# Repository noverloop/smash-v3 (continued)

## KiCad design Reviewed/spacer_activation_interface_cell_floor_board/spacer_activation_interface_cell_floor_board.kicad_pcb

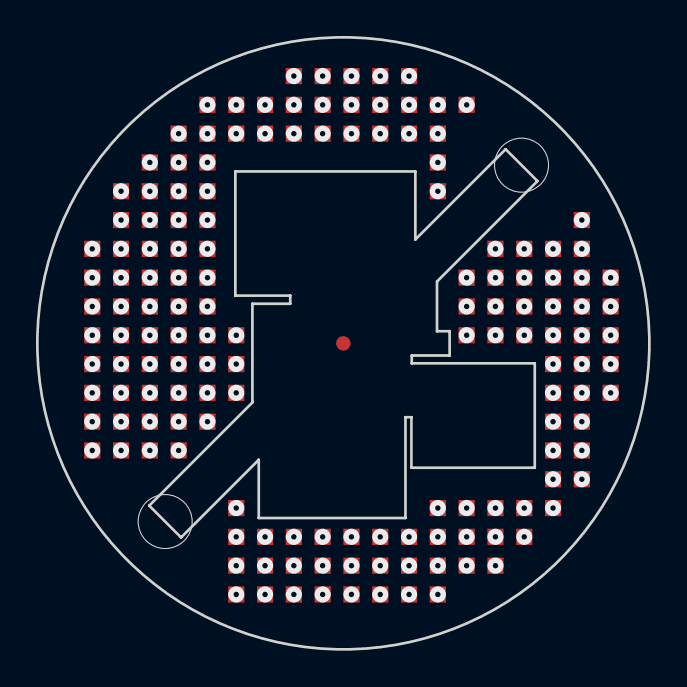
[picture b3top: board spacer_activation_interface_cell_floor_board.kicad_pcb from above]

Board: 2 copper layers, 34.0 x 34.0 mm, 3 parts (1 on the bottom side), 46 nets, no tracks yet.

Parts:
J_spacer_activation_interface_cell_floor_board_top: LGA_lands; J_spacer_activation_interface_cell_floor_board_top
P_spacer_activation_interface_cell_floor_board_bot: LGA_lands; P_spacer_activation_interface_cell_floor_board_bot
SP_activation_interface_cell_floor_board: SP_activation_interface_cell_floor_board; Spacer_Mechanical_34mm

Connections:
3V3: J_spacer_activation_interface_cell_floo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.1, J_spacer_activation_interface_cell_floo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.47, J_spacer_activation_interface_cell_floo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.52, P_spacer_activation_interface_cell_floo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.1, P_spacer_activation_interface_cell_floo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.47, P_spacer_activation_interface_cell_floo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.52
3V3_AON: J_spacer_activation_interface_cell_floo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.2, J_spacer_activation_interface_cell_floo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.48, P_spacer_activation_interface_cell_floo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.2, P_spacer_activation_interface_cell_floo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.48
ACTIVATE_CONFIRM: J_spacer_activation_interface_cell_floo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.3, P_spacer_activation_interface_cell_floo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.3
ACTIVATE_SET: J_spacer_activation_interface_cell_floo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.4, P_spacer_activation_interface_cell_floo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.4
BAT_PROT: J_spacer_activation_interface_cell_floo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.5, J_spacer_activation_interface_cell_floo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.49, P_spacer_activation_interface_cell_floo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.5, P_spacer_activation_interface_cell_floo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.49
BAT_RAW: J_spacer_activation_interface_cell_floo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.6, J_spacer_activation_interface_cell_floo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.50, P_spacer_activation_interface_cell_floo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.6, P_spacer_activation_interface_cell_floo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.50
BOOT0: J_spacer_activation_interface_cell_floo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.7, P_spacer_activation_interface_cell_floo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.7
COMP_5V: J_spacer_activation_interface_cell_floo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.8, J_spacer_activation_interface_cell_floo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.51, P_spacer_activation_interface_cell_floo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.8, P_spacer_activation_interface_cell_floo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.51
COMP_SWDCLK: J_spacer_activation_interface_cell_floo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.9, P_spacer_activation_interface_cell_floo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.9
COMP_SWDIO: J_spacer_activation_interface_cell_floo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.10, P_spacer_activation_interface_cell_floo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.10
EXT_CAN_RX: J_spacer_activation_interface_cell_floo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.11, P_spacer_activation_interface_cell_floo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.11
EXT_CAN_TX: J_spacer_activation_interface_cell_floo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.12, P_spacer_activation_interface_cell_floo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.12
FIN1_AOUT1: J_spacer_activation_interface_cell_floo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.13, P_spacer_activation_interface_cell_floo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.13
FIN1_AOUT2: J_spacer_activation_interface_cell_floo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.14, P_spacer_activation_interface_cell_floo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.14
FIN1_BOUT1: J_spacer_activation_interface_cell_floo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.15, P_spacer_activation_interface_cell_floo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.15
FIN1_BOUT2: J_spacer_activation_interface_cell_floo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.16, P_spacer_activation_interface_cell_floo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.16
FIN2_AOUT1: J_spacer_activation_interface_cell_floo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.17, P_spacer_activation_interface_cell_floo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.17
FIN2_AOUT2: J_spacer_activation_interface_cell_floo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.18, P_spacer_activation_interface_cell_floo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.18
FIN2_BOUT1: J_spacer_activation_interface_cell_floo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.19, P_spacer_activation_interface_cell_floo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.19
FIN2_BOUT2: J_spacer_activation_interface_cell_floo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.20, P_spacer_activation_interface_cell_floo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.20
FIN3_AOUT1: J_spacer_activation_interface_cell_floo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.21, P_spacer_activation_interface_cell_floo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.21
FIN3_AOUT2: J_spacer_activation_interface_cell_floo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.22, P_spacer_activation_interface_cell_floo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.22
FIN3_BOUT1: J_spacer_activation_interface_cell_floo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.23, P_spacer_activation_interface_cell_floo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.23
FIN3_BOUT2: J_spacer_activation_interface_cell_floo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.24, P_spacer_activation_interface_cell_floo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.24
FIN4_AOUT1: J_spacer_activation_interface_cell_floo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.25, P_spacer_activation_interface_cell_floo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.25
FIN4_AOUT2: J_spacer_activation_interface_cell_floo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.26, P_spacer_activation_interface_cell_floo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.26
FIN4_BOUT1: J_spacer_activation_interface_cell_floo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.27, P_spacer_activation_interface_cell_floo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.27
FIN4_BOUT2: J_spacer_activation_interface_cell_floo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.28, P_spacer_activation_interface_cell_floo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.28
FIN_HALL: J_spacer_activation_interface_cell_floo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.29, P_spacer_activation_interface_cell_floo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.29
FLEX_GND: J_spacer_activation_interface_cell_floo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.30, J_spacer_activation_interface_cell_floo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.53, J_spacer_activation_interface_cell_floo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.54, J_spacer_activation_interface_cell_floo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.55, J_spacer_activation_interface_cell_floo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.56, J_spacer_activation_interface_cell_floo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.57, J_spacer_activation_interface_cell_floo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.58, J_spacer_activation_interface_cell_floo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.59, J_spacer_activation_interface_cell_floo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.60, J_spacer_activation_interface_cell_floo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.61, J_spacer_activation_interface_cell_floo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.62, J_spacer_activation_interface_cell_floo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.63, J_spacer_activation_interface_cell_floo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.64, J_spacer_activation_interface_cell_floo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.65, J_spacer_activation_interface_cell_floo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.66, J_spacer_activation_interface_cell_floo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.67, J_spacer_activation_interface_cell_floo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.68, J_spacer_activation_interface_cell_floo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.69, J_spacer_activation_interface_cell_floo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.70, J_spacer_activation_interface_cell_floo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.71, J_spacer_activation_interface_cell_floo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.72, J_spacer_activation_interface_cell_floo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.73, J_spacer_activation_interface_cell_floo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.74, J_spacer_activation_interface_cell_floo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.75, J_spacer_activation_interface_cell_floo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.76, J_spacer_activation_interface_cell_floo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.77, J_spacer_activation_interface_cell_floo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.78, J_spacer_activation_interface_cell_floo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.79, J_spacer_activation_interface_cell_floo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.80, J_spacer_activation_interface_cell_floo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.81, J_spacer_activation_interface_cell_floo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.82, J_spacer_activation_interface_cell_floo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.83, J_spacer_activation_interface_cell_floo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.84, J_spacer_activation_interface_cell_floo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.85, J_spacer_activation_interface_cell_floo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.86, J_spacer_activation_interface_cell_floo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.87, J_spacer_activation_interface_cell_floo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.88, J_spacer_activation_interface_cell_floo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.89, J_spacer_activation_interface_cell_floo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.90, J_spacer_activation_interface_cell_floo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.91, J_spacer_activation_interface_cell_floo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.92, J_spacer_activation_interface_cell_floo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.93, J_spacer_activation_interface_cell_floo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.94, J_spacer_activation_interface_cell_floo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.95, J_spacer_activation_interface_cell_floo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.96, J_spacer_activation_interface_cell_floo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.97, J_spacer_activation_interface_cell_floo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.98, J_spacer_activation_interface_cell_floo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.99, J_spacer_activation_interface_cell_floo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.100, J_spacer_activation_interface_cell_floo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.101, J_spacer_activation_interface_cell_floo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.102, J_spacer_activation_interface_cell_floo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.103, J_spacer_activation_interface_cell_floo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.104, J_spacer_activation_interface_cell_floo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.105, J_spacer_activation_interface_cell_floo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.106, J_spacer_activation_interface_cell_floo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.107, J_spacer_activation_interface_cell_floo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.108, J_spacer_activation_interface_cell_floo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.109, J_spacer_activation_interface_cell_floo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.110, J_spacer_activation_interface_cell_floo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.111, J_spacer_activation_interface_cell_floo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.112, J_spacer_activation_interface_cell_floo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.113, J_spacer_activation_interface_cell_floo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.114, J_spacer_activation_interface_cell_floo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.115, J_spacer_activation_interface_cell_floo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.116, J_spacer_activation_interface_cell_floo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.117, J_spacer_activation_interface_cell_floo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.118, J_spacer_activation_interface_cell_floo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.119, J_spacer_activation_interface_cell_floo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.120, J_spacer_activation_interface_cell_floo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.121, J_spacer_activation_interface_cell_floo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.122, J_spacer_activation_interface_cell_floo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.123, J_spacer_activation_interface_cell_floo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.124, J_spacer_activation_interface_cell_floo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.125, J_spacer_activation_interface_cell_floo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.126, J_spacer_activation_interface_cell_floo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.127, J_spacer_activation_interface_cell_floo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.128, J_spacer_activation_interface_cell_floo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.129, J_spacer_activation_interface_cell_floo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.130, J_spacer_activation_interface_cell_floo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.131, J_spacer_activation_interface_cell_floo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.132, J_spacer_activation_interface_cell_floo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.133, J_spacer_activation_interface_cell_floo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.134, J_spacer_activation_interface_cell_floo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.135, J_spacer_activation_interface_cell_floo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.136, J_spacer_activation_interface_cell_floo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.137, J_spacer_activation_interface_cell_floo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.138, J_spacer_activation_interface_cell_floo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.139, J_spacer_activation_interface_cell_floo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.140, J_spacer_activation_interface_cell_floo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.141, J_spacer_activation_interface_cell_floo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.142, J_spacer_activation_interface_cell_floo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.143, J_spacer_activation_interface_cell_floo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.144, J_spacer_activation_interface_cell_floo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.145, J_spacer_activation_interface_cell_floo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.146, J_spacer_activation_interface_cell_floo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.147, J_spacer_activation_interface_cell_floo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.148, J_spacer_activation_interface_cell_floo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.149, J_spacer_activation_interface_cell_floo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.150, P_spacer_activation_interface_cell_floo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.30, P_spacer_activation_interface_cell_floo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.53, P_spacer_activation_interface_cell_floo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.54, P_spacer_activation_interface_cell_floo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.55, P_spacer_activation_interface_cell_floo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.56, P_spacer_activation_interface_cell_floo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.57, P_spacer_activation_interface_cell_floo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.58, P_spacer_activation_interface_cell_floo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.59, P_spacer_activation_interface_cell_floo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.60, P_spacer_activation_interface_cell_floo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.61, P_spacer_activation_interface_cell_floo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.62, P_spacer_activation_interface_cell_floo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.63, P_spacer_activation_interface_cell_floo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.64, P_spacer_activation_interface_cell_floo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.65, P_spacer_activation_interface_cell_floo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.66, P_spacer_activation_interface_cell_floo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.67, P_spacer_activation_interface_cell_floo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.68, P_spacer_activation_interface_cell_floo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.69, P_spacer_activation_interface_cell_floo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.70, P_spacer_activation_interface_cell_floo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.71, P_spacer_activation_interface_cell_floo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.72, P_spacer_activation_interface_cell_floo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.73, P_spacer_activation_interface_cell_floo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.74, P_spacer_activation_interface_cell_floo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.75, P_spacer_activation_interface_cell_floo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.76, P_spacer_activation_interface_cell_floo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.77, P_spacer_activation_interface_cell_floo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.78, P_spacer_activation_interface_cell_floo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.79, P_spacer_activation_interface_cell_floo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.80, P_spacer_activation_interface_cell_floo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.81, P_spacer_activation_interface_cell_floo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.82, P_spacer_activation_interface_cell_floo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.83, P_spacer_activation_interface_cell_floo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.84, P_spacer_activation_interface_cell_floo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.85, P_spacer_activation_interface_cell_floo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.86, P_spacer_activation_interface_cell_floo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.87, P_spacer_activation_interface_cell_floo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.88, P_spacer_activation_interface_cell_floo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.89, P_spacer_activation_interface_cell_floo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.90, P_spacer_activation_interface_cell_floo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.91, P_spacer_activation_interface_cell_floo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.92, P_spacer_activation_interface_cell_floo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.93, P_spacer_activation_interface_cell_floo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.94, P_spacer_activation_interface_cell_floo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.95, P_spacer_activation_interface_cell_floo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.96, P_spacer_activation_interface_cell_floo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.97, P_spacer_activation_interface_cell_floo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.98, P_spacer_activation_interface_cell_floo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.99, P_spacer_activation_interface_cell_floo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.100, P_spacer_activation_interface_cell_floo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.101, P_spacer_activation_interface_cell_floo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.102, P_spacer_activation_interface_cell_floo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.103, P_spacer_activation_interface_cell_floo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.104, P_spacer_activation_interface_cell_floo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.105, P_spacer_activation_interface_cell_floo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.106, P_spacer_activation_interface_cell_floo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.107, P_spacer_activation_interface_cell_floo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.108, P_spacer_activation_interface_cell_floo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.109, P_spacer_activation_interface_cell_floo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.110, P_spacer_activation_interface_cell_floo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.111, P_spacer_activation_interface_cell_floo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.112, P_spacer_activation_interface_cell_floo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.113, P_spacer_activation_interface_cell_floo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.114, P_spacer_activation_interface_cell_floo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.115, P_spacer_activation_interface_cell_floo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.116, P_spacer_activation_interface_cell_floo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.117, P_spacer_activation_interface_cell_floo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.118, P_spacer_activation_interface_cell_floo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.119, P_spacer_activation_interface_cell_floo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.120, P_spacer_activation_interface_cell_floo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.121, P_spacer_activation_interface_cell_floo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.122, P_spacer_activation_interface_cell_floo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.123, P_spacer_activation_interface_cell_floo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.124, P_spacer_activation_interface_cell_floo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.125, P_spacer_activation_interface_cell_floo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.126, P_spacer_activation_interface_cell_floo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.127, P_spacer_activation_interface_cell_floo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.128, P_spacer_activation_interface_cell_floo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.129, P_spacer_activation_interface_cell_floo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.130, P_spacer_activation_interface_cell_floo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.131, P_spacer_activation_interface_cell_floo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.132, P_spacer_activation_interface_cell_floo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.133, P_spacer_activation_interface_cell_floo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.134, P_spacer_activation_interface_cell_floo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.135, P_spacer_activation_interface_cell_floo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.136, P_spacer_activation_interface_cell_floo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.137, P_spacer_activation_interface_cell_floo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.138, P_spacer_activation_interface_cell_floo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.139, P_spacer_activation_interface_cell_floo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.140, P_spacer_activation_interface_cell_floo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.141, P_spacer_activation_interface_cell_floo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.142, P_spacer_activation_interface_cell_floo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.143, P_spacer_activation_interface_cell_floo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.144, P_spacer_activation_interface_cell_floo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.145, P_spacer_activation_interface_cell_floo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.146, P_spacer_activation_interface_cell_floo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.147, P_spacer_activation_interface_cell_floo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.148, P_spacer_activation_interface_cell_floo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.149, P_spacer_activation_interface_cell_floo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.150, SP_activation_interface_cell_floor_board.1
GPIO_EXT_0: J_spacer_activation_interface_cell_floo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.31, P_spacer_activation_interface_cell_floo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.31
GPIO_EXT_1: J_spacer_activation_interface_cell_floo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.32, P_spacer_activation_interface_cell_floo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.32
GPIO_EXT_2: J_spacer_activation_interface_cell_floo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.33, P_spacer_activation_interface_cell_floo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.33
GPIO_EXT_3: J_spacer_activation_interface_cell_floo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.34, P_spacer_activation_interface_cell_floo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.34
H3LIS_INT1: J_spacer_activation_interface_cell_floo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.35, P_spacer_activation_interface_cell_floo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.35
I2C3_SCL: J_spacer_activation_interface_cell_floo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.36, P_spacer_activation_interface_cell_floo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.36
I2C3_SDA: J_spacer_activation_interface_cell_floo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.37, P_spacer_activation_interface_cell_floo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.37
JUMP_WAKE: J_spacer_activation_interface_cell_floo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.38, P_spacer_activation_interface_cell_floo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.38
NRST: J_spacer_activation_interface_cell_floo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.39, P_spacer_activation_interface_cell_floo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.39
SWO: J_spacer_activation_interface_cell_floo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.40, P_spacer_activation_interface_cell_floo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.40
SYS_I2C_SCL: J_spacer_activation_interface_cell_floo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.41, P_spacer_activation_interface_cell_floo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.41
SYS_I2C_SDA: J_spacer_activation_interface_cell_floo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.42, P_spacer_activation_interface_cell_floo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.42
SYS_SPI_CS_FIN: J_spacer_activation_interface_cell_floo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.43, P_spacer_activation_interface_cell_floo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.43
SYS_SPI_MISO: J_spacer_activation_interface_cell_floo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.44, P_spacer_activation_interface_cell_floo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.44
SYS_SPI_MOSI: J_spacer_activation_interface_cell_floo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.45, P_spacer_activation_interface_cell_floo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.45
SYS_SPI_SCLK: J_spacer_activation_interface_cell_floo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.46, P_spacer_activation_interface_cell_floo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.46

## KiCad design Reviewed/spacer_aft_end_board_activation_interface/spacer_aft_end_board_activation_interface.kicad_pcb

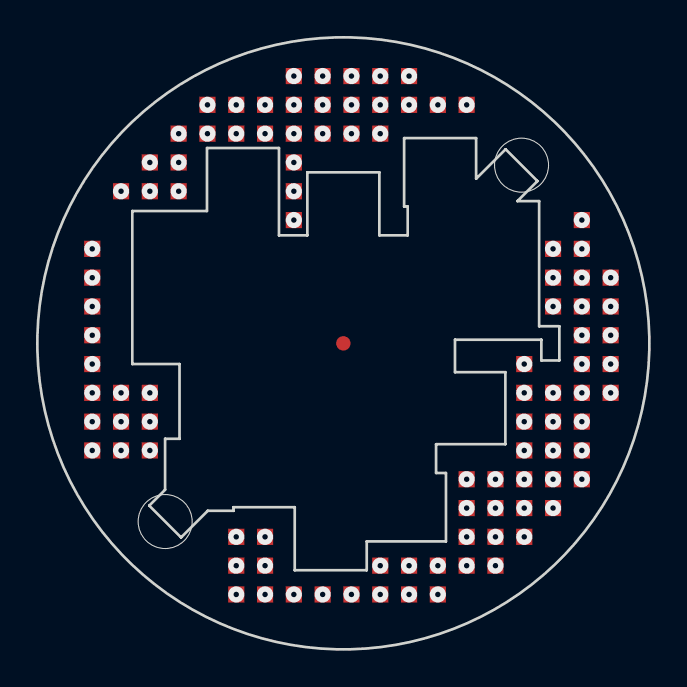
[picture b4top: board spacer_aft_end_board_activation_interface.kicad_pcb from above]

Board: 2 copper layers, 34.0 x 34.0 mm, 3 parts (1 on the bottom side), 44 nets, no tracks yet.

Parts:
J_spacer_aft_end_board_activation_interface_top: LGA_lands; J_spacer_aft_end_board_activation_interface_top
P_spacer_aft_end_board_activation_interface_bot: LGA_lands; P_spacer_aft_end_board_activation_interface_bot
SP_aft_end_board_activation_interface: SP_aft_end_board_activation_interface; Spacer_Mechanical_34mm

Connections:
3V3: J_spacer_aft_end_board_activation_inter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.1, J_spacer_aft_end_board_activation_inter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.45, J_spacer_aft_end_board_activation_inter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.51, P_spacer_aft_end_board_activation_inter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.1, P_spacer_aft_end_board_activation_inter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.45, P_spacer_aft_end_board_activation_inter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.51
3V3_AON: J_spacer_aft_end_board_activation_inter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.2, J_spacer_aft_end_board_activation_inter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.46, P_spacer_aft_end_board_activation_inter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.2, P_spacer_aft_end_board_activation_inter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.46
ACTIVATE_CONFIRM: J_spacer_aft_end_board_activation_inter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.3, P_spacer_aft_end_board_activation_inter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.3
ACTIVATE_HV: J_spacer_aft_end_board_activation_inter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.28, J_spacer_aft_end_board_activation_inter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.50, P_spacer_aft_end_board_activation_inter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.28, P_spacer_aft_end_board_activation_inter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.50
ACTIVATE_SET: J_spacer_aft_end_board_activation_inter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.4, P_spacer_aft_end_board_activation_inter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.4
BAT_PROT: J_spacer_aft_end_board_activation_inter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.5, J_spacer_aft_end_board_activation_inter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.47, P_spacer_aft_end_board_activation_inter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.5, P_spacer_aft_end_board_activation_inter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.47
BAT_RAW: J_spacer_aft_end_board_activation_inter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.6, J_spacer_aft_end_board_activation_inter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.48, P_spacer_aft_end_board_activation_inter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.6, P_spacer_aft_end_board_activation_inter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.48
BOOT0: J_spacer_aft_end_board_activation_inter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.7, P_spacer_aft_end_board_activation_inter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.7
COMP_5V: J_spacer_aft_end_board_activation_inter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.8, J_spacer_aft_end_board_activation_inter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.49, P_spacer_aft_end_board_activation_inter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.8, P_spacer_aft_end_board_activation_inter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.49
COMP_SWDCLK: J_spacer_aft_end_board_activation_inter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.9, P_spacer_aft_end_board_activation_inter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.9
COMP_SWDIO: J_spacer_aft_end_board_activation_inter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.10, P_spacer_aft_end_board_activation_inter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.10
EXT_CAN_RX: J_spacer_aft_end_board_activation_inter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.16, P_spacer_aft_end_board_activation_inter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.16
EXT_CAN_TX: J_spacer_aft_end_board_activation_inter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.12, P_spacer_aft_end_board_activation_inter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.12
FIN1_AOUT1: J_spacer_aft_end_board_activation_inter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.13, P_spacer_aft_end_board_activation_inter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.13
FIN1_AOUT2: J_spacer_aft_end_board_activation_inter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.14, P_spacer_aft_end_board_activation_inter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.14
FIN1_BOUT1: J_spacer_aft_end_board_activation_inter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.15, P_spacer_aft_end_board_activation_inter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.15
FIN1_BOUT2: J_spacer_aft_end_board_activation_inter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.11, P_spacer_aft_end_board_activation_inter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.11
FIN2_AOUT1: J_spacer_aft_end_board_activation_inter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.17, P_spacer_aft_end_board_activation_inter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.17
FIN2_AOUT2: J_spacer_aft_end_board_activation_inter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.18, P_spacer_aft_end_board_activation_inter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.18
FIN2_BOUT1: J_spacer_aft_end_board_activation_inter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.19, P_spacer_aft_end_board_activation_inter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.19
FIN2_BOUT2: J_spacer_aft_end_board_activation_inter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.20, P_spacer_aft_end_board_activation_inter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.20
FIN3_AOUT1: J_spacer_aft_end_board_activation_inter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.21, P_spacer_aft_end_board_activation_inter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.21
FIN3_AOUT2: J_spacer_aft_end_board_activation_inter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.22, P_spacer_aft_end_board_activation_inter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.22
FIN3_BOUT1: J_spacer_aft_end_board_activation_inter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.23, P_spacer_aft_end_board_activation_inter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.23
FIN3_BOUT2: J_spacer_aft_end_board_activation_inter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.24, P_spacer_aft_end_board_activation_inter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.24
FIN4_AOUT1: J_spacer_aft_end_board_activation_inter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.25, P_spacer_aft_end_board_activation_inter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.25
FIN4_AOUT2: J_spacer_aft_end_board_activation_inter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.30, P_spacer_aft_end_board_activation_inter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.30
FIN4_BOUT1: J_spacer_aft_end_board_activation_inter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.27, P_spacer_aft_end_board_activation_inter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.27
FIN4_BOUT2: J_spacer_aft_end_board_activation_inter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.26, P_spacer_aft_end_board_activation_inter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.26
FIN_HALL: J_spacer_aft_end_board_activation_inter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.29, P_spacer_aft_end_board_activation_inter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.29
FLEX_GND: J_spacer_aft_end_board_activation_inter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.31, J_spacer_aft_end_board_activation_inter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.52, J_spacer_aft_end_board_activation_inter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.53, J_spacer_aft_end_board_activation_inter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.54, J_spacer_aft_end_board_activation_inter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.55, J_spacer_aft_end_board_activation_inter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.56, J_spacer_aft_end_board_activation_inter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.57, J_spacer_aft_end_board_activation_inter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.58, J_spacer_aft_end_board_activation_inter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.59, J_spacer_aft_end_board_activation_inter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.60, J_spacer_aft_end_board_activation_inter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.61, J_spacer_aft_end_board_activation_inter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.62, J_spacer_aft_end_board_activation_inter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.63, J_spacer_aft_end_board_activation_inter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.64, J_spacer_aft_end_board_activation_inter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.65, J_spacer_aft_end_board_activation_inter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.66, J_spacer_aft_end_board_activation_inter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.67, J_spacer_aft_end_board_activation_inter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.68, J_spacer_aft_end_board_activation_inter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.69, J_spacer_aft_end_board_activation_inter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.70, J_spacer_aft_end_board_activation_inter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.71, J_spacer_aft_end_board_activation_inter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.72, J_spacer_aft_end_board_activation_inter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.73, J_spacer_aft_end_board_activation_inter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.74, J_spacer_aft_end_board_activation_inter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.75, J_spacer_aft_end_board_activation_inter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.76, J_spacer_aft_end_board_activation_inter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.77, J_spacer_aft_end_board_activation_inter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.78, J_spacer_aft_end_board_activation_inter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.79, J_spacer_aft_end_board_activation_inter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.80, J_spacer_aft_end_board_activation_inter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.81, J_spacer_aft_end_board_activation_inter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.82, J_spacer_aft_end_board_activation_inter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.83, J_spacer_aft_end_board_activation_inter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.84, J_spacer_aft_end_board_activation_inter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.85, J_spacer_aft_end_board_activation_inter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.86, J_spacer_aft_end_board_activation_inter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.87, J_spacer_aft_end_board_activation_inter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.88, J_spacer_aft_end_board_activation_inter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.89, J_spacer_aft_end_board_activation_inter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.90, J_spacer_aft_end_board_activation_inter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.91, J_spacer_aft_end_board_activation_inter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.92, J_spacer_aft_end_board_activation_inter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.93, J_spacer_aft_end_board_activation_inter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.94, J_spacer_aft_end_board_activation_inter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.95, J_spacer_aft_end_board_activation_inter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.96, J_spacer_aft_end_board_activation_inter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.97, J_spacer_aft_end_board_activation_inter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.98, P_spacer_aft_end_board_activation_inter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.31, P_spacer_aft_end_board_activation_inter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.52, P_spacer_aft_end_board_activation_inter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.53, P_spacer_aft_end_board_activation_inter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.54, P_spacer_aft_end_board_activation_inter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.55, P_spacer_aft_end_board_activation_inter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.56, P_spacer_aft_end_board_activation_inter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.57, P_spacer_aft_end_board_activation_inter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.58, P_spacer_aft_end_board_activation_inter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.59, P_spacer_aft_end_board_activation_inter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.60, P_spacer_aft_end_board_activation_inter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.61, P_spacer_aft_end_board_activation_inter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.62, P_spacer_aft_end_board_activation_inter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.63, P_spacer_aft_end_board_activation_inter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.64, P_spacer_aft_end_board_activation_inter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.65, P_spacer_aft_end_board_activation_inter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.66, P_spacer_aft_end_board_activation_inter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.67, P_spacer_aft_end_board_activation_inter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.68, P_spacer_aft_end_board_activation_inter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.69, P_spacer_aft_end_board_activation_inter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.70, P_spacer_aft_end_board_activation_inter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.71, P_spacer_aft_end_board_activation_inter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.72, P_spacer_aft_end_board_activation_inter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.73, P_spacer_aft_end_board_activation_inter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.74, P_spacer_aft_end_board_activation_inter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.75, P_spacer_aft_end_board_activation_inter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.76, P_spacer_aft_end_board_activation_inter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.77, P_spacer_aft_end_board_activation_inter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.78, P_spacer_aft_end_board_activation_inter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.79, P_spacer_aft_end_board_activation_inter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.80, P_spacer_aft_end_board_activation_inter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.81, P_spacer_aft_end_board_activation_inter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.82, P_spacer_aft_end_board_activation_inter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.83, P_spacer_aft_end_board_activation_inter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.84, P_spacer_aft_end_board_activation_inter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.85, P_spacer_aft_end_board_activation_inter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.86, P_spacer_aft_end_board_activation_inter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.87, P_spacer_aft_end_board_activation_inter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.88, P_spacer_aft_end_board_activation_inter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.89, P_spacer_aft_end_board_activation_inter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.90, P_spacer_aft_end_board_activation_inter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.91, P_spacer_aft_end_board_activation_inter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.92, P_spacer_aft_end_board_activation_inter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.93, P_spacer_aft_end_board_activation_inter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.94, P_spacer_aft_end_board_activation_inter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.95, P_spacer_aft_end_board_activation_inter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.96, P_spacer_aft_end_board_activation_inter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.97, P_spacer_aft_end_board_activation_inter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.98, SP_aft_end_board_activation_interface.1
GPIO_EXT_0: J_spacer_aft_end_board_activation_inter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.32, P_spacer_aft_end_board_activation_inter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.32
GPIO_EXT_1: J_spacer_aft_end_board_activation_inter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.33, P_spacer_aft_end_board_activation_inter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.33
GPIO_EXT_2: J_spacer_aft_end_board_activation_inter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.34, P_spacer_aft_end_board_activation_inter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.34
GPIO_EXT_3: J_spacer_aft_end_board_activation_inter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.35, P_spacer_aft_end_board_activation_inter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.35
JUMP_WAKE: J_spacer_aft_end_board_activation_inter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.36, P_spacer_aft_end_board_activation_inter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.36
NRST: J_spacer_aft_end_board_activation_inter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.37, P_spacer_aft_end_board_activation_inter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.37
SWO: J_spacer_aft_end_board_activation_inter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.38, P_spacer_aft_end_board_activation_inter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.38
SYS_I2C_SCL: J_spacer_aft_end_board_activation_inter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.39, P_spacer_aft_end_board_activation_inter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.39
SYS_I2C_SDA: J_spacer_aft_end_board_activation_inter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.40, P_spacer_aft_end_board_activation_inter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.40
SYS_SPI_CS_FIN: J_spacer_aft_end_board_activation_inter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.41, P_spacer_aft_end_board_activation_inter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.41
SYS_SPI_MISO: J_spacer_aft_end_board_activation_inter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.42, P_spacer_aft_end_board_activation_inter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.42
SYS_SPI_MOSI: J_spacer_aft_end_board_activation_inter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.43, P_spacer_aft_end_board_activation_inter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.43
SYS_SPI_SCLK: J_spacer_aft_end_board_activation_inter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.44, P_spacer_aft_end_board_activation_inter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.44

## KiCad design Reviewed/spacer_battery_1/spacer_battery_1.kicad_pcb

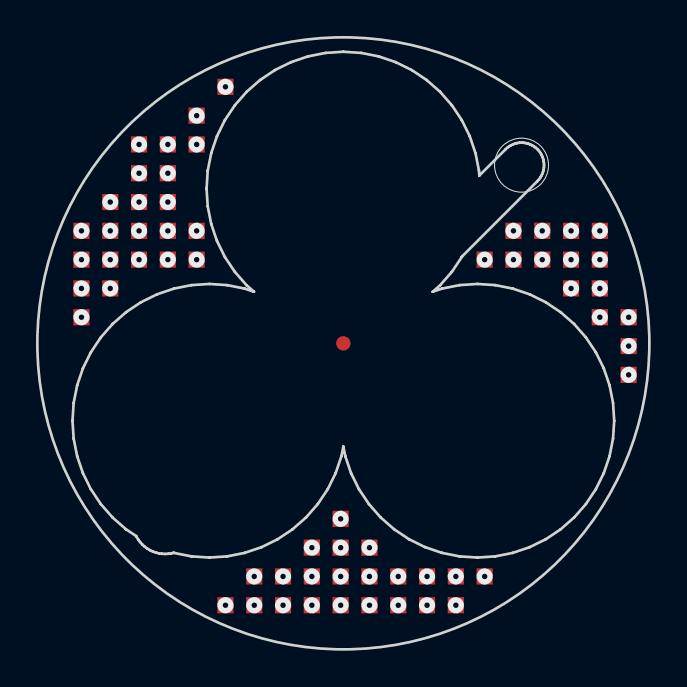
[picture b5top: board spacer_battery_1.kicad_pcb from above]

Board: 2 copper layers, 34.0 x 34.0 mm, 3 parts (1 on the bottom side), 46 nets, no tracks yet.

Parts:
J_spacer_battery_1_top: LGA_lands; J_spacer_battery_1_top
P_spacer_battery_1_bot: LGA_lands; P_spacer_battery_1_bot
SP_battery_1: SP_battery_1; Spacer_Mechanical_34mm

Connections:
3V3: J_spacer_battery_1_top.23, J_spacer_battery_1_top.47, J_spacer_battery_1_top.52, P_spacer_battery_1_bot.23, P_spacer_battery_1_bot.47, P_spacer_battery_1_bot.52
3V3_AON: J_spacer_battery_1_top.24, J_spacer_battery_1_top.48, P_spacer_battery_1_bot.24, P_spacer_battery_1_bot.48
ACTIVATE_CONFIRM: J_spacer_battery_1_top.3, P_spacer_battery_1_bot.3
ACTIVATE_SET: J_spacer_battery_1_top.4, P_spacer_battery_1_bot.4
BAT_PROT: J_spacer_battery_1_top.5, J_spacer_battery_1_top.49, P_spacer_battery_1_bot.5, P_spacer_battery_1_bot.49
BAT_RAW: J_spacer_battery_1_top.6, J_spacer_battery_1_top.50, P_spacer_battery_1_bot.6, P_spacer_battery_1_bot.50
BOOT0: J_spacer_battery_1_top.7, P_spacer_battery_1_bot.7
COMP_5V: J_spacer_battery_1_top.8, J_spacer_battery_1_top.51, P_spacer_battery_1_bot.8, P_spacer_battery_1_bot.51
COMP_SWDCLK: J_spacer_battery_1_top.9, P_spacer_battery_1_bot.9
COMP_SWDIO: J_spacer_battery_1_top.10, P_spacer_battery_1_bot.10
EXT_CAN_RX: J_spacer_battery_1_top.11, P_spacer_battery_1_bot.11
EXT_CAN_TX: J_spacer_battery_1_top.14, P_spacer_battery_1_bot.14
FIN1_AOUT1: J_spacer_battery_1_top.13, P_spacer_battery_1_bot.13
FIN1_AOUT2: J_spacer_battery_1_top.12, P_spacer_battery_1_bot.12
FIN1_BOUT1: J_spacer_battery_1_top.15, P_spacer_battery_1_bot.15
FIN1_BOUT2: J_spacer_battery_1_top.16, P_spacer_battery_1_bot.16
FIN2_AOUT1: J_spacer_battery_1_top.17, P_spacer_battery_1_bot.17
FIN2_AOUT2: J_spacer_battery_1_top.18, P_spacer_battery_1_bot.18
FIN2_BOUT1: J_spacer_battery_1_top.19, P_spacer_battery_1_bot.19
FIN2_BOUT2: J_spacer_battery_1_top.20, P_spacer_battery_1_bot.20
FIN3_AOUT1: J_spacer_battery_1_top.21, P_spacer_battery_1_bot.21
FIN3_AOUT2: J_spacer_battery_1_top.22, P_spacer_battery_1_bot.22
FIN3_BOUT1: J_spacer_battery_1_top.1, P_spacer_battery_1_bot.1
FIN3_BOUT2: J_spacer_battery_1_top.2, P_spacer_battery_1_bot.2
FIN4_AOUT1: J_spacer_battery_1_top.25, P_spacer_battery_1_bot.25
FIN4_AOUT2: J_spacer_battery_1_top.26, P_spacer_battery_1_bot.26
FIN4_BOUT1: J_spacer_battery_1_top.27, P_spacer_battery_1_bot.27
FIN4_BOUT2: J_spacer_battery_1_top.28, P_spacer_battery_1_bot.28
FIN_HALL: J_spacer_battery_1_top.29, P_spacer_battery_1_bot.29
FLEX_GND: J_spacer_battery_1_top.30, J_spacer_battery_1_top.53, J_spacer_battery_1_top.54, J_spacer_battery_1_top.55, J_spacer_battery_1_top.56, J_spacer_battery_1_top.57, J_spacer_battery_1_top.58, J_spacer_battery_1_top.59, J_spacer_battery_1_top.60, P_spacer_battery_1_bot.30, P_spacer_battery_1_bot.53, P_spacer_battery_1_bot.54, P_spacer_battery_1_bot.55, P_spacer_battery_1_bot.56, P_spacer_battery_1_bot.57, P_spacer_battery_1_bot.58, P_spacer_battery_1_bot.59, P_spacer_battery_1_bot.60, SP_battery_1.1
GPIO_EXT_0: J_spacer_battery_1_top.31, P_spacer_battery_1_bot.31
GPIO_EXT_1: J_spacer_battery_1_top.32, P_spacer_battery_1_bot.32
GPIO_EXT_2: J_spacer_battery_1_top.33, P_spacer_battery_1_bot.33
GPIO_EXT_3: J_spacer_battery_1_top.34, P_spacer_battery_1_bot.34
H3LIS_INT1: J_spacer_battery_1_top.35, P_spacer_battery_1_bot.35
I2C3_SCL: J_spacer_battery_1_top.36, P_spacer_battery_1_bot.36
I2C3_SDA: J_spacer_battery_1_top.37, P_spacer_battery_1_bot.37
JUMP_WAKE: J_spacer_battery_1_top.38, P_spacer_battery_1_bot.38
NRST: J_spacer_battery_1_top.39, P_spacer_battery_1_bot.39
SWO: J_spacer_battery_1_top.40, P_spacer_battery_1_bot.40
SYS_I2C_SCL: J_spacer_battery_1_top.41, P_spacer_battery_1_bot.41
SYS_I2C_SDA: J_spacer_battery_1_top.42, P_spacer_battery_1_bot.42
SYS_SPI_CS_FIN: J_spacer_battery_1_top.43, P_spacer_battery_1_bot.43
SYS_SPI_MISO: J_spacer_battery_1_top.44, P_spacer_battery_1_bot.44
SYS_SPI_MOSI: J_spacer_battery_1_top.45, P_spacer_battery_1_bot.45
SYS_SPI_SCLK: J_spacer_battery_1_top.46, P_spacer_battery_1_bot.46

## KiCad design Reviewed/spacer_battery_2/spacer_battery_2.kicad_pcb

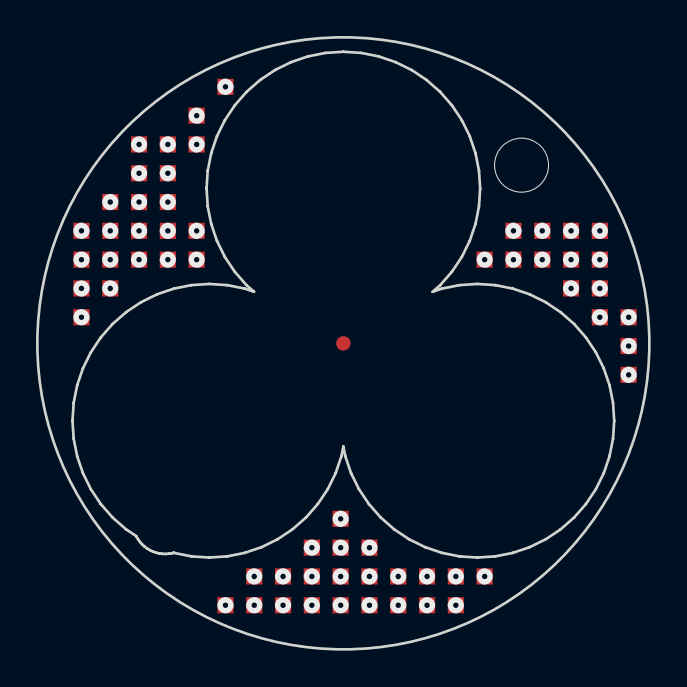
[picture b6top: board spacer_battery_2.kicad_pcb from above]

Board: 2 copper layers, 34.0 x 34.0 mm, 3 parts (1 on the bottom side), 46 nets, no tracks yet.

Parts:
J_spacer_battery_2_top: LGA_lands; J_spacer_battery_2_top
P_spacer_battery_2_bot: LGA_lands; P_spacer_battery_2_bot
SP_battery_2: SP_battery_2; Spacer_Mechanical_34mm

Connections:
3V3: J_spacer_battery_2_top.23, J_spacer_battery_2_top.47, J_spacer_battery_2_top.52, P_spacer_battery_2_bot.23, P_spacer_battery_2_bot.47, P_spacer_battery_2_bot.52
3V3_AON: J_spacer_battery_2_top.24, J_spacer_battery_2_top.48, P_spacer_battery_2_bot.24, P_spacer_battery_2_bot.48
ACTIVATE_CONFIRM: J_spacer_battery_2_top.3, P_spacer_battery_2_bot.3
ACTIVATE_SET: J_spacer_battery_2_top.4, P_spacer_battery_2_bot.4
BAT_PROT: J_spacer_battery_2_top.5, J_spacer_battery_2_top.49, P_spacer_battery_2_bot.5, P_spacer_battery_2_bot.49
BAT_RAW: J_spacer_battery_2_top.6, J_spacer_battery_2_top.50, P_spacer_battery_2_bot.6, P_spacer_battery_2_bot.50
BOOT0: J_spacer_battery_2_top.7, P_spacer_battery_2_bot.7
COMP_5V: J_spacer_battery_2_top.8, J_spacer_battery_2_top.51, P_spacer_battery_2_bot.8, P_spacer_battery_2_bot.51
COMP_SWDCLK: J_spacer_battery_2_top.9, P_spacer_battery_2_bot.9
COMP_SWDIO: J_spacer_battery_2_top.10, P_spacer_battery_2_bot.10
EXT_CAN_RX: J_spacer_battery_2_top.11, P_spacer_battery_2_bot.11
EXT_CAN_TX: J_spacer_battery_2_top.14, P_spacer_battery_2_bot.14
FIN1_AOUT1: J_spacer_battery_2_top.13, P_spacer_battery_2_bot.13
FIN1_AOUT2: J_spacer_battery_2_top.12, P_spacer_battery_2_bot.12
FIN1_BOUT1: J_spacer_battery_2_top.15, P_spacer_battery_2_bot.15
FIN1_BOUT2: J_spacer_battery_2_top.16, P_spacer_battery_2_bot.16
FIN2_AOUT1: J_spacer_battery_2_top.17, P_spacer_battery_2_bot.17
FIN2_AOUT2: J_spacer_battery_2_top.18, P_spacer_battery_2_bot.18
FIN2_BOUT1: J_spacer_battery_2_top.19, P_spacer_battery_2_bot.19
FIN2_BOUT2: J_spacer_battery_2_top.20, P_spacer_battery_2_bot.20
FIN3_AOUT1: J_spacer_battery_2_top.21, P_spacer_battery_2_bot.21
FIN3_AOUT2: J_spacer_battery_2_top.22, P_spacer_battery_2_bot.22
FIN3_BOUT1: J_spacer_battery_2_top.1, P_spacer_battery_2_bot.1
FIN3_BOUT2: J_spacer_battery_2_top.2, P_spacer_battery_2_bot.2
FIN4_AOUT1: J_spacer_battery_2_top.25, P_spacer_battery_2_bot.25
FIN4_AOUT2: J_spacer_battery_2_top.26, P_spacer_battery_2_bot.26
FIN4_BOUT1: J_spacer_battery_2_top.27, P_spacer_battery_2_bot.27
FIN4_BOUT2: J_spacer_battery_2_top.28, P_spacer_battery_2_bot.28
FIN_HALL: J_spacer_battery_2_top.29, P_spacer_battery_2_bot.29
FLEX_GND: J_spacer_battery_2_top.30, J_spacer_battery_2_top.53, J_spacer_battery_2_top.54, J_spacer_battery_2_top.55, J_spacer_battery_2_top.56, J_spacer_battery_2_top.57, J_spacer_battery_2_top.58, J_spacer_battery_2_top.59, J_spacer_battery_2_top.60, P_spacer_battery_2_bot.30, P_spacer_battery_2_bot.53, P_spacer_battery_2_bot.54, P_spacer_battery_2_bot.55, P_spacer_battery_2_bot.56, P_spacer_battery_2_bot.57, P_spacer_battery_2_bot.58, P_spacer_battery_2_bot.59, P_spacer_battery_2_bot.60, SP_battery_2.1
GPIO_EXT_0: J_spacer_battery_2_top.31, P_spacer_battery_2_bot.31
GPIO_EXT_1: J_spacer_battery_2_top.32, P_spacer_battery_2_bot.32
GPIO_EXT_2: J_spacer_battery_2_top.33, P_spacer_battery_2_bot.33
GPIO_EXT_3: J_spacer_battery_2_top.34, P_spacer_battery_2_bot.34
H3LIS_INT1: J_spacer_battery_2_top.35, P_spacer_battery_2_bot.35
I2C3_SCL: J_spacer_battery_2_top.36, P_spacer_battery_2_bot.36
I2C3_SDA: J_spacer_battery_2_top.37, P_spacer_battery_2_bot.37
JUMP_WAKE: J_spacer_battery_2_top.38, P_spacer_battery_2_bot.38
NRST: J_spacer_battery_2_top.39, P_spacer_battery_2_bot.39
SWO: J_spacer_battery_2_top.40, P_spacer_battery_2_bot.40
SYS_I2C_SCL: J_spacer_battery_2_top.41, P_spacer_battery_2_bot.41
SYS_I2C_SDA: J_spacer_battery_2_top.42, P_spacer_battery_2_bot.42
SYS_SPI_CS_FIN: J_spacer_battery_2_top.43, P_spacer_battery_2_bot.43
SYS_SPI_MISO: J_spacer_battery_2_top.44, P_spacer_battery_2_bot.44
SYS_SPI_MOSI: J_spacer_battery_2_top.45, P_spacer_battery_2_bot.45
SYS_SPI_SCLK: J_spacer_battery_2_top.46, P_spacer_battery_2_bot.46

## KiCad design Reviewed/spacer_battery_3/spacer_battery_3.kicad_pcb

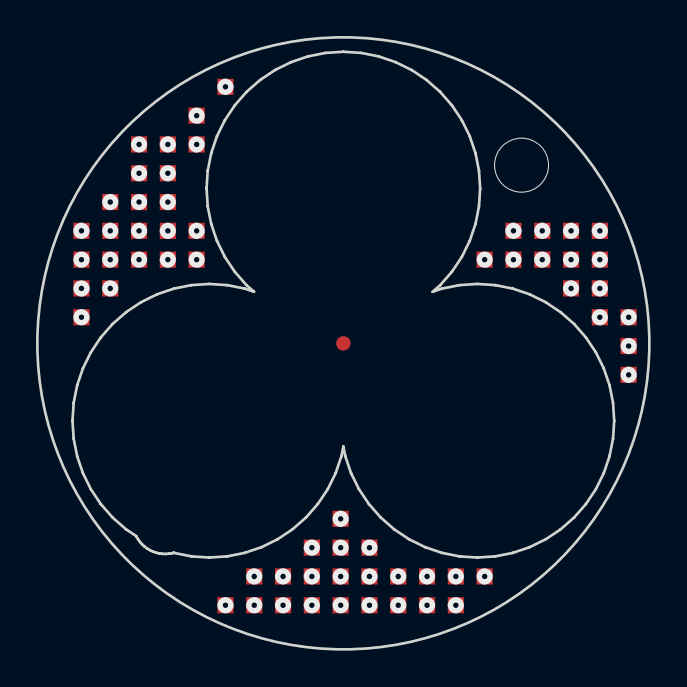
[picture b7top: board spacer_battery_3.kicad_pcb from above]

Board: 2 copper layers, 34.0 x 34.0 mm, 3 parts (1 on the bottom side), 46 nets, no tracks yet.

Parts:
J_spacer_battery_3_top: LGA_lands; J_spacer_battery_3_top
P_spacer_battery_3_bot: LGA_lands; P_spacer_battery_3_bot
SP_battery_3: SP_battery_3; Spacer_Mechanical_34mm

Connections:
3V3: J_spacer_battery_3_top.23, J_spacer_battery_3_top.47, J_spacer_battery_3_top.52, P_spacer_battery_3_bot.23, P_spacer_battery_3_bot.47, P_spacer_battery_3_bot.52
3V3_AON: J_spacer_battery_3_top.24, J_spacer_battery_3_top.48, P_spacer_battery_3_bot.24, P_spacer_battery_3_bot.48
ACTIVATE_CONFIRM: J_spacer_battery_3_top.3, P_spacer_battery_3_bot.3
ACTIVATE_SET: J_spacer_battery_3_top.4, P_spacer_battery_3_bot.4
BAT_PROT: J_spacer_battery_3_top.5, J_spacer_battery_3_top.49, P_spacer_battery_3_bot.5, P_spacer_battery_3_bot.49
BAT_RAW: J_spacer_battery_3_top.6, J_spacer_battery_3_top.50, P_spacer_battery_3_bot.6, P_spacer_battery_3_bot.50
BOOT0: J_spacer_battery_3_top.7, P_spacer_battery_3_bot.7
COMP_5V: J_spacer_battery_3_top.8, J_spacer_battery_3_top.51, P_spacer_battery_3_bot.8, P_spacer_battery_3_bot.51
COMP_SWDCLK: J_spacer_battery_3_top.9, P_spacer_battery_3_bot.9
COMP_SWDIO: J_spacer_battery_3_top.10, P_spacer_battery_3_bot.10
EXT_CAN_RX: J_spacer_battery_3_top.11, P_spacer_battery_3_bot.11
EXT_CAN_TX: J_spacer_battery_3_top.14, P_spacer_battery_3_bot.14
FIN1_AOUT1: J_spacer_battery_3_top.13, P_spacer_battery_3_bot.13
FIN1_AOUT2: J_spacer_battery_3_top.12, P_spacer_battery_3_bot.12
FIN1_BOUT1: J_spacer_battery_3_top.15, P_spacer_battery_3_bot.15
FIN1_BOUT2: J_spacer_battery_3_top.16, P_spacer_battery_3_bot.16
FIN2_AOUT1: J_spacer_battery_3_top.17, P_spacer_battery_3_bot.17
FIN2_AOUT2: J_spacer_battery_3_top.18, P_spacer_battery_3_bot.18
FIN2_BOUT1: J_spacer_battery_3_top.19, P_spacer_battery_3_bot.19
FIN2_BOUT2: J_spacer_battery_3_top.20, P_spacer_battery_3_bot.20
FIN3_AOUT1: J_spacer_battery_3_top.21, P_spacer_battery_3_bot.21
FIN3_AOUT2: J_spacer_battery_3_top.22, P_spacer_battery_3_bot.22
FIN3_BOUT1: J_spacer_battery_3_top.1, P_spacer_battery_3_bot.1
FIN3_BOUT2: J_spacer_battery_3_top.2, P_spacer_battery_3_bot.2
FIN4_AOUT1: J_spacer_battery_3_top.25, P_spacer_battery_3_bot.25
FIN4_AOUT2: J_spacer_battery_3_top.26, P_spacer_battery_3_bot.26
FIN4_BOUT1: J_spacer_battery_3_top.27, P_spacer_battery_3_bot.27
FIN4_BOUT2: J_spacer_battery_3_top.28, P_spacer_battery_3_bot.28
FIN_HALL: J_spacer_battery_3_top.29, P_spacer_battery_3_bot.29
FLEX_GND: J_spacer_battery_3_top.30, J_spacer_battery_3_top.53, J_spacer_battery_3_top.54, J_spacer_battery_3_top.55, J_spacer_battery_3_top.56, J_spacer_battery_3_top.57, J_spacer_battery_3_top.58, J_spacer_battery_3_top.59, J_spacer_battery_3_top.60, P_spacer_battery_3_bot.30, P_spacer_battery_3_bot.53, P_spacer_battery_3_bot.54, P_spacer_battery_3_bot.55, P_spacer_battery_3_bot.56, P_spacer_battery_3_bot.57, P_spacer_battery_3_bot.58, P_spacer_battery_3_bot.59, P_spacer_battery_3_bot.60, SP_battery_3.1
GPIO_EXT_0: J_spacer_battery_3_top.31, P_spacer_battery_3_bot.31
GPIO_EXT_1: J_spacer_battery_3_top.32, P_spacer_battery_3_bot.32
GPIO_EXT_2: J_spacer_battery_3_top.33, P_spacer_battery_3_bot.33
GPIO_EXT_3: J_spacer_battery_3_top.34, P_spacer_battery_3_bot.34
H3LIS_INT1: J_spacer_battery_3_top.35, P_spacer_battery_3_bot.35
I2C3_SCL: J_spacer_battery_3_top.36, P_spacer_battery_3_bot.36
I2C3_SDA: J_spacer_battery_3_top.37, P_spacer_battery_3_bot.37
JUMP_WAKE: J_spacer_battery_3_top.38, P_spacer_battery_3_bot.38
NRST: J_spacer_battery_3_top.39, P_spacer_battery_3_bot.39
SWO: J_spacer_battery_3_top.40, P_spacer_battery_3_bot.40
SYS_I2C_SCL: J_spacer_battery_3_top.41, P_spacer_battery_3_bot.41
SYS_I2C_SDA: J_spacer_battery_3_top.42, P_spacer_battery_3_bot.42
SYS_SPI_CS_FIN: J_spacer_battery_3_top.43, P_spacer_battery_3_bot.43
SYS_SPI_MISO: J_spacer_battery_3_top.44, P_spacer_battery_3_bot.44
SYS_SPI_MOSI: J_spacer_battery_3_top.45, P_spacer_battery_3_bot.45
SYS_SPI_SCLK: J_spacer_battery_3_top.46, P_spacer_battery_3_bot.46
